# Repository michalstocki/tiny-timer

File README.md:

# Minutnik na ATtiny13A

Firmware w czystym C (`avr-gcc -Os`, bez Arduino core), instrukcja montażu na płytce stykowej, programowanie przez Arduino UNO, kalibracja i testy odbiorcze. Materiały dla użytkownika są po polsku.

| Co | Gdzie |
| --- | --- |
| Instrukcja montażu (kroki, adresy otworów, rysunki, sprawdzenia) | [docs/instrukcja-montazu.md](docs/instrukcja-montazu.md) |
| Programowanie: ArduinoISP, fuse'y, wgrywanie | [docs/programowanie.md](docs/programowanie.md) |
| Kalibracja czasu (OSCCAL) | [docs/kalibracja.md](docs/kalibracja.md) |
| Testy odbiorcze (tabela do wypełnienia) | [docs/testy-odbiorcze.md](docs/testy-odbiorcze.md) |
| Diagnostyka | [docs/diagnostyka.md](docs/diagnostyka.md) |
| Plan B: ATtiny25/45/85 z ramką i dzwonkiem | [docs/plan-b.md](docs/plan-b.md) |
| Netlista i mapa pinów | [docs/schemat.md](docs/schemat.md) |
| Gotowe pliki `.hex` i raport `avr-size` | `dist/` |
| Źródła firmware i `Makefile` | `firmware/` |
| Generator rysunków/instrukcji i weryfikacja sieci | `tools/breadboard/` |
| Symulacja logiki firmware na komputerze | `tools/sim/` |

## Szybki start

```bash
cd firmware
make                                    # buduje i drukuje rozmiary (avr-gcc z PATH lub z Arduino IDE)
make sig   PORT=/dev/cu.usbmodemXXXX    # Etap 1: sygnatura 0x1e9007 (ATtiny w gnieździe programatora)
make fuses PORT=/dev/cu.usbmodemXXXX    # Etap 2
make flash PROG=test_tone PORT=...      # Etapy 3-5: test_tone, test_display, test_buttons
make flash PROG=timer PORT=...          # Etap 6
```

Weryfikacja bez sprzętu:

```bash
tools/sim/run.sh                                 # logika minutnika (ATtiny13A)
SIM_FLAGS="-DFEATURE_BAR=1 -DFEATURE_BELL=1" tools/sim/run.sh   # plan B
SIM_TARGET=calib tools/sim/run.sh                # program kalibracyjny
cd tools/breadboard && python3 design.py && python3 test_design.py
```

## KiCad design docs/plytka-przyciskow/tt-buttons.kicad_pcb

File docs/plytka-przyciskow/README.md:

# Płytka przycisków (obudowa klin 4)

Trzy przyciski Omron B3F-4055 (S3 „−”, S1 „run”, S2 „+”) i cztery przewody do pól KEY płytki głównej. Są dwie wersje o tym samym położeniu przycisków, otworów M2 i pól przewodów:

| Wersja | Dla kogo |
| --- | --- |
| **[Płytka drukowana TT-BTN](#płytka-drukowana-tt-btn-zamówienie-na-pcbway)** (54 × 16 mm, 2 warstwy) | zalecana: bez pracy warsztatowej, zamówienie razem z płytką główną |
| [Płytka uniwersalna](#płytka-przycisków-na-płytce-uniwersalnej) (50 × 16 mm, raster 2,54) | gdy masz płytkę uniwersalną pod ręką i nie chcesz czekać na fabrykę |

## Płytka drukowana TT-BTN (zamówienie na PCBWay)

| Plik | Co to |
| --- | --- |
| [`tt-buttons.kicad_pcb`](tt-buttons.kicad_pcb) | projekt dla KiCada (format v7, sprawdzony w KiCadzie 10.0.7): obrys, stopki, sieci, ścieżki, opisy |
| [`produkcja/tt-buttons-gerber.zip`](produkcja/tt-buttons-gerber.zip) | **plik do wysłania do fabryki**: 7 warstw Gerber, wiercenia PTH i NPTH (Excellon, mm), plik zadania `.gbrjob` |
| `produkcja/` (reszta) | rozpakowane Gerbery, raporty DRC KiCada, mapy wierceń (poza zipem), podglądy `kicad-F.svg` i `kicad-B.svg` |
| [`plytka-przyciskow-pcb-top.png`](plytka-przyciskow-pcb-top.png), [`plytka-przyciskow-pcb-bottom.png`](plytka-przyciskow-pcb-bottom.png) | render KiCada obu stron |

### Zamówienie

Płytka główna ([`docs/plytka-glowna/`](../plytka-glowna/README.md)) i płytka przycisków to **dwa osobne projekty i dwa osobne zamówienia**, oba jako „Single pieces”. Wrzuć oba do jednego koszyka, wtedy wysyłka jest jedna.

| Parametr w formularzu PCBWay | Płytka przycisków | Płytka główna |
| --- | --- | --- |
| Board type | Single pieces | Single pieces |
| Different design in panel | 1 | 1 |
| Size | **54 × 16 mm** | 40 × 24 mm |
| Quantity | 5 | 5 |
| Layers / Material / Thickness | 2 / FR-4 / 1,6 mm | 2 / FR-4 / 1,6 mm |
| Pozostałe | domyślne (HASL, zielona maska, biały opis, miedź 1 oz) | jak w [README płytki głównej](../plytka-glowna/README.md#parametry-do-zamówienia-typowa-fabryka-2-warstwowa-np-jlcpcb-lub-pcbway) |

**Dlaczego nie jeden plik z obiema płytkami (panel).** Sprawdziłem w kalkulatorze PCBWay (15.11.2026, 2 warstwy, FR-4 1,6 mm, opcje domyślne, ceny bez wysyłki). Najniższa stawka obejmuje tylko 5 sztuk **jednego** projektu do 100 × 100 mm. Każde połączenie płytek w jednym pliku podnosi cenę:

| Wariant | Sztuk | Cena |
| --- | --- | --- |
| 1 projekt, Single pieces (40 × 24, 54 × 16 albo do 100 × 100 mm) | 5 | **5,00 USD** |
| to samo | 10 / 20 | 18,69 / 22,33 USD |
| 2 projekty w jednym pliku, Single pieces | 5 | 27,00 USD |
| panel klienta z mostkami, 1 zestaw (główna + przyciski) | 5 paneli | 36,10 USD |
| panel klienta, 2 zestawy, 100 × 50 mm | 5 paneli | 39,99 USD |
| panel klienta, 3 zestawy, 100 × 100 mm | 5 paneli | 47,04 USD |

Dwie osobne płytki to więc 10 USD za 5 kompletów. PCBWay nie nacina też płytek tak małych jak nasze: według jej zasad V-cut wymaga co najmniej 60 × 45 mm. Każdy panel trzeba by łączyć mostkami z otworami, a to ich formularz liczy jako panel klienta („Panel by Customer”, zob. [Confirm the panel way of the boards](https://www.pcbway.com/helpcenter/panel_issues/Confirm_the_panel_way_of_the_boards.html), [PCB Panel Creation](https://www.pcbway.com/pcb_prototype/PCB_Panel_Creation.html), [V-Scoring](https://www.pcbway.com/pcb_prototype/PCB_V_Scoring.html)). Ceny są orientacyjne: kalkulator zaznacza, że cenę ostateczną ustala PCBWay po weryfikacji, i ceny mogą się zmienić.

### Projekt

- **Zarys 54 × 16 mm** z narożnikami R2, o 2 mm szerszy z każdej strony niż płytka uniwersalna. Przy 50 mm otwory skrajnych nóżek (rozstaw 12,5 mm według karty) leżałyby 0,4 mm od krawędzi, a pola wychodziłyby poza płytkę. Przyciski, otwory M2 i pola przewodów są w tych samych miejscach względem obudowy, a w tabeli niżej współrzędne są przesunięte o 2 mm. Szerszy zarys sprawdziłem w modelu obudowy klin 4 (`TT_BB_EXTRA=2` w [`build_wedge4.py`](../../tools/enclosure/build_wedge4.py)): 0 kolizji w 104 parach, zdejmowanie pokrywy bez kolizji.
- **Stopka B3F-4055 według karty:** 4 pola Ø2,2 z otworem Ø1,2 w rozstawie 12,5 × 5,0 mm i dwa otwory **Ø1,8 bez metalizacji na kołki ustalające** (9,0 mm od siebie). Kołków nie trzeba ścinać.
- **Pola przewodów** Ø2,0 z otworem 1,2 mm, jak pola KEY na płytce głównej. Są w tych samych miejscach co oczka G4, G6, N4 i N2 na płytce uniwersalnej. KEY1 (GND) ma pole kwadratowe, tak jak na płytce głównej. Opisy K1…K4 są na obu stronach.
- **Ścieżki** 0,30 mm, ręcznie, pod kątem 45°. Strona lutowania (B.Cu): rzędy nóżek każdego przycisku, GND od S1 do S2 i odejścia do K1, K2 i K4. Strona elementów (F.Cu): jedna ścieżka PB4 od S3 przez K3, osią przycisków pod S1, do S2. Schemat jest ten sam co niżej, nie ma przewodów rozdzielczych.
- **Otwory M2** Ø2,2 bez metalizacji. Miedź trzyma się z daleka od łba wkręta (od strony lutowania) i od słupka pokrywy (od strony elementów): ścieżki co najmniej 2,3 mm od osi, pola 3,4 mm.
- Opisy: oznaczenia S1…S3 i symbole −, RUN, + na stronie elementów. Na stronie lutowania napis TT-BTN v1.0 i strzałka „glosnik ->” wskazująca stronę głośnika. Napisy „TOP” i „BOT” w miedzi, jak na płytce głównej (kontrola, czy warstwy nie są zamienione).

| Element | Położenie [mm] od lewego dolnego narożnika (widok od strony elementów) |
| --- | --- |
| S3 „−”, S1 „run”, S2 „+” (środki) | 9,22 / 27,00 / 44,78; y = 8,00 |
| otwory M2 Ø2,2 | (18,11; 2,92) i (35,89; 13,08) |
| K1 GND (kwadratowe), K2 PB3 | (35,89; 8,00), (35,89; 2,92) |
| K3 PB4, K4 do R6 | (18,11; 8,00), (18,11; 13,08) |

### Montaż

1. Sprawdź przyciski multimetrem (krok 0 niżej). Wynik decyduje o schemacie.
2. Włóż trzy przyciski od strony elementów (kołki wchodzą w otwory Ø1,8), dociśnij do laminatu i zalutuj od strony lutowania (12 lutów). Nie myj płytki z przyciskami.
3. Przewody KEY1…KEY4 przełóż od strony lutowania przez pola K1…K4 i zalutuj od strony elementów, z końcówką do 1 mm (nad płytką jest 6,8 mm do sufitu pokrywy). Kolory i pola płytki głównej jak w tabeli „Połączenia na płytce” niżej.
4. Kontrola multimetrem jak w kroku 10 niżej. Montaż w pokrywie: dwa wkręty M2 × 6 od strony lutowania, lewa krawędź (strzałka „glosnik ->”) od strony głośnika.

### Co sprawdziłem

- **Kontrola własna** ([`tools/pcb/fab_buttons.py`](../../tools/pcb/fab_buttons.py)): każda z 4 sieci w jednym kawałku, odstęp miedzi co najmniej 0,25 mm (najmniejszy jest **0,35 mm**), miedź co najmniej 0,5 mm od krawędzi, otwory kołków i M2 ze strefami wolnymi od miedzi. Test ujemny: usunięta ścieżka, ścieżka przy polu innej sieci i ścieżka przy M2 są wykrywane. Pierwsza wersja trasy przechodziła 0,13 mm od narożnika kwadratowego pola KEY1. Wykrył to DRC KiCada, bo moja kontrola liczyła pola jako okrągłe. Kontrola liczy teraz kwadraty jako kwadraty i na starej trasie podaje te same odległości co KiCad.
- **KiCad 10.0.7** ([`export_fab.sh`](../../tools/pcb/export_fab.sh)): DRC bez błędów, 0 niepołączonych pól. Zostało 9 ostrzeżeń o braku biblioteki `TT` (stopki są wbudowane w plik). Gerbery i wiercenia: PTH Ø1,2 (12 nóżek i 4 pola przewodów), NPTH Ø1,8 (6 kołków) i Ø2,2 (2 × M2).
- **Nie sprawdziłem** podglądu Gerberów w PCBWay (wymaga wgrania pliku na ich stronę) ani dopasowania na fizycznym B3F-4055. Po wgraniu zipa sprawdź, czy PCBWay rozpoznał 2 warstwy i wymiar 54 × 16 mm.

### Regeneracja

```bash
python3 tools/pcb/fab_buttons.py                                                                 # kontrola + tt-buttons.kicad_pcb
bash tools/pcb/export_fab.sh docs/plytka-przyciskow/tt-buttons.kicad_pcb docs/plytka-przyciskow/produkcja   # DRC KiCada, Gerbery, zip
```

## Płytka przycisków na płytce uniwersalnej

Trzy przyciski Omron B3F-4055 (S3 „−”, S1 „run”, S2 „+”) na kawałku jednostronnej płytki uniwersalnej **50 × 16 mm**, z czterema przewodami do pól KEY płytki głównej. Zarys, otwory M2 i rozstaw przycisków są zgodne z [obudową klin 4](../obudowa-klin-4/README.md#5-płytka-przycisków-na-płytce-uniwersalnej) (dane: [`pcb-layout.json`](../pcb-klin3/pcb-layout.json), klucz `button_board`).

**Do druku: [`plytka-przyciskow-szablon.pdf`](plytka-przyciskow-szablon.pdf)** (A4, 4 strony):

| Strona | Treść |
| --- | --- |
| 1 | **Szablon 1:1** od strony elementów: zarys z narożnikami R2, siatka oczek, otwory M2 Ø2,2, obrysy przycisków, tabela współrzędnych, linijka kontrolna 100 mm |
| 2 | **Połączenia** od strony lutowania w skali 3:1: adresy oczek, 6 przewodów rozdzielczych, 4 pola KEY, lista przewodów z kolorami i długościami |
| 3 | **Schemat elektryczny**, wnętrze przycisku wg karty, kontrola multimetrem |
| 4 | Lista części i narzędzi, kolejność montażu, najczęstsze pułapki |

Te same strony jako SVG: `plytka-przyciskow-{szablon,polaczenia,schemat,montaz}.svg`. Generator i kontrola projektu: [`tools/pcb/button_board.py`](../../tools/pcb/button_board.py).

```bash
python3 tools/pcb/button_board.py           # kontrola + PDF/SVG w tym katalogu (wymaga rsvg-convert)
python3 tools/pcb/button_board.py --check   # tylko kontrola
```

## Założenie: przycisk zgodny z kartą

Projekt przyjmuje budowę z karty Omron B3F (A070-E1-08, s. 6, model B3F-4055 „projected plunger, bez nóżki masy”):

| Co | Wartość z karty |
| --- | --- |
| Połączenia wewnętrzne (widok z góry) | **4–3 i 2–1 połączone na stałe**, wciśnięcie zwiera górny rząd z dolnym |
| Nóżki | 4 szt., **12,5 × 5,0 mm** (±0,1), otwory w płytce Ø1,2 (±0,05); blaszki ok. 1,0 × 0,3 mm (odczyt z rysunku), 3,5 mm pod korpusem |
| Kołki ustalające | 2 szt. Ø1,6 (otwory Ø1,8), **9,0 mm** od siebie, na osi między kolumnami nóżek |
| Korpus, wysokość, trzpień | 12 × 12 mm, 7,3 mm nad płytką (korpus 4,3), trzpień 3,8 × 3,8 mm |
| Siła, skok | 2,55 ±0,69 N, skok 0,3 mm; obciążenie 1…50 mA, 3…24 V; mycie niemożliwe |

To rozstrzyga sprzeczność z wcześniejszej specyfikacji (`docs/pcb/specyfikacja-obudowy-dla-agenta.md`, punkt 7: „wg pomiaru właściciela 5 mm”): **nóżki połączone na stałe dzieli 12,5 mm**, nie 5 mm. Numery nóżek nie są nadrukowane na obudowie przycisku, więc w projekcie rozróżnia się je po położeniu: para nóżek rozstawionych o 12,5 mm to jeden „rząd”.

Skoro założenie decyduje o schemacie, pierwszym krokiem montażu jest **sprawdzenie ciągłości na samych przyciskach** (strona 3 i 4 PDF). Jeśli wynik wyjdzie odwrotnie, nie lutuj dalej.

## Płytka uniwersalna

- Jednostronna FR4 **1,6 mm**, raster **2,54 mm**, **osobne pola lutownicze** (nie płytka paskowa: paski zwarłyby nóżki). Kawałek co najmniej 55 × 20 mm, wygodniej 70 × 30 mm.
- Przed zakupem lub użyciem sprawdź raster: skrajne oczka rzędu na płytce mają trafić w kropki A i T szablonu (19 odstępów = 48,26 mm). Płytki o rastrze 2,5 mm się nie nadają.
- Oczka Ø1,0 mogą być za ciasne dla blaszki 1,0 × 0,3 mm (przekątna ok. 1,05 mm): jeśli nóżka wchodzi z oporem, rozwierć oczko pod nóżkę do Ø1,2, zgodnie z kartą.

## Geometria i raster

Siatka oczek leży tak, że wszystkie nóżki przycisków trafiają w oczka. Adres oczka to **kolumna A…T + rząd 1…7** w widoku od strony elementów (x w prawo, y w górę), jak na szablonie.

| Element | Położenie [mm] od lewego dolnego narożnika | Oczko |
| --- | --- | --- |
| przycisk S3 „−” (środek) | 7,22; 8,00 | nóżki A3, F3 (dół), A5, F5 (góra) |
| przycisk S1 „run” | 25,00; 8,00 | H3, M3, H5, M5 |
| przycisk S2 „+” | 42,78; 8,00 | O3, T3, O5, T5 |
| otwór M2-1 Ø2,2 | 16,11; 2,92 | G2 |
| otwór M2-2 Ø2,2 | 33,89; 13,08 | N6 |

- Pierwsze oczko (A1) jest w (0,87; 0,38), ostatnie (T7) w (49,13; 15,62). Raster ma 20 kolumn × 7 rzędów, a środki przycisków leżą w połowie oczka (x) i na rzędzie 4 (y).
- Rozstaw oczek 12,70 mm kontra 12,50 mm w karcie: oczka są o 0,10 mm na każdą stronę dalej niż otwory zalecane, w granicach tolerancji karty (nóżki są sprężyste). Odchyłka w osi y to 0,04 mm. Generator sprawdza to przy każdym uruchomieniu.
- **Skrajne rzędy oczek (1 i 7) leżą 0,38 mm od krawędzi, więc linia cięcia przetnie ich oczka.** Nie są używane. Nie da się tego uniknąć bez zmiany obudowy: rzędy nóżek (y = 5,46 i 10,54) wyznaczają fazę rastra. Skrajne kolumny (A i T) są 0,87 mm od krawędzi i zostają prawie całe.
- Dwa otwory M2 leżą na oczkach, po przekątnej, pomiędzy przyciskami (słupki w pokrywie nie wchodzą w korpusy: sprawdzone wymiarowo).

## Schemat

| Przycisk | Górny rząd (nóżki 4–3) | Dolny rząd (nóżki 2–1) | Zwiera |
| --- | --- | --- | --- |
| S1 „run” | KEY1 (GND) | KEY2 (PB3) | KEY1–KEY2 |
| S2 „+” | KEY1 (GND) | KEY3 (PB4) | KEY1–KEY3 |
| S3 „−” | KEY4 (do R6, potem GND) | KEY3 (PB4) | KEY3–KEY4 |

Zgodne z [`docs/schemat.md`](../schemat.md): PB3 ma wewnętrzny pull-up, PB4 ma R5 8,2 kΩ do VCC, a „−” przechodzi przez R6 8,2 kΩ do GND (R6 jest na płytce głównej). Kontrola w generatorze buduje sieć z rysunku (nóżki, przewody, wewnętrzne połączenia przycisku) i sprawdza wszystkie 8 kombinacji wciśniętych przycisków: puszczone dają cztery osobne pola, a każdy przycisk zwiera dokładnie swoją parę. Wykrywa to błędy typu przewód na złym rzędzie albo pole KEY w złym oczku (sprawdziłem na celowo zepsutych wariantach).

## Połączenia na płytce

Wszystko po stronie lutowania, widok na stronie 2 PDF (obrócony jak kartka wokół osi pionowej, więc kolumny idą T → A).

| Nr | Od | Do | Sieć | Kolor | Trasa |
| --- | --- | --- | --- | --- | --- |
| W1 | M5 (S1, nóżka 3) | N4 | GND | czarny | 3,6 mm |
| W2 | O5 (S2, nóżka 4) | N4 | GND | czarny | 3,6 mm |
| W3 | M3 (S1, nóżka 1) | N2 | PB3 | pomarańczowy | 3,6 mm |
| W4 | F3 (S3, nóżka 1) | G4 | PB4 | niebieski | 3,6 mm |
| W5 | O3 (S2, nóżka 2) | G4 | PB4 | niebieski | 22,9 mm, rowkiem między rzędami 3 i 4 |
| W6 | F5 (S3, nóżka 3) | G6 | KEY4 | zielony | 3,6 mm |
| KEY1 | N4 | płytka główna | GND | czarny | |
| KEY2 | N2 | płytka główna | PB3 | pomarańczowy | |
| KEY3 | G4 | płytka główna | PB4 | niebieski | |
| KEY4 | G6 | płytka główna | do R6 | zielony | |

- Pola przewodu leżą w dwóch kolumnach między przyciskami (G i N), poza korpusami, więc przewód można przewlec z oczka na stronę elementów. Dwa przewody idą do jednej kolumny, dwa do drugiej: kabel z płytki głównej wystarczy rozdzielić na pary.
- Pozostałe nóżki (np. H5, T3) są po prostu przylutowane: wewnętrzne połączenie przycisku łączy je z sąsiadką.
- Oczka N4 i G4 mają po trzy przewody (kabel + dwa rozdzielcze): użyj cienkich przewodów rozdzielczych Ø0,25 (wire-wrap AWG30).
- Przewód W5 biegnie 3,8 mm od osi wkręta M2 w G2 (łeb Ø4 ma promień 2 mm). Generator pilnuje, żeby trasy przewodów były co najmniej 2,3 mm, a używane oczka co najmniej 3,4 mm od osi M2.
- Kolory kabla do płytki głównej to propozycja. Ważne, żeby zapisać, który przewód jest którym polem KEY.

## Instrukcja montażu

**Części:** 3 × Omron B3F-4055 (nie B3F-4155: ma piątą nóżkę), płytka uniwersalna jak wyżej, 6 przewodów rozdzielczych w izolacji Ø0,25 (razem ok. 10 cm), 4 linki 0,14 mm² w kolorach z tabeli, 2 wkręty samogwintujące M2 × 6, cyna z topnikiem bezmyjnym. **Narzędzia:** wiertła Ø1,0 i Ø2,2 (opcjonalnie Ø1,2), imadło, piła do laminatu lub miniszlifierka, pilnik, nożyk, szczypce tnące, multimetr, lutownica z grotem 1…2 mm.

0. **Sprawdź przyciski** (przed czymkolwiek). Multimetrem w zakresie ciągłości: nóżki rozstawione o 12,5 mm w jednym rzędzie (4–3 oraz 2–1) mają ciągłość zawsze, a nóżki w tej samej kolumnie (4–2, 3–1; 5,0 mm) tylko po wciśnięciu. Jeśli jest odwrotnie, przycisk nie jest zgodny z kartą: zatrzymaj się i zmierz sześć par nóżek.
1. **Wydrukuj stronę 1 w skali 100 %** (w oknie drukowania „Rzeczywisty rozmiar”, bez „Dopasuj do strony”). Odcinek 100 mm i kwadrat 20 × 20 mm sprawdź linijką. Dokładność wydruku nie ma tu znaczenia dla oczek (te są na płytce), ale ma dla linii cięcia i otworów M2.
2. **Przyłóż szablon do płytki** tak, by kropki szablonu (także szare, poza zarysem) pokryły się z oczkami płytki; zamocuj kawałkiem taśmy lub klejem w sztyfcie. Środki M2 nakłuj igłą przez papier (krzyżyki wskazują środek), zdejmij szablon. Linię cięcia możesz odrysować rysikiem.
3. **Wywierć M2:** płytka w imadle na drewnianej podkładce, najpierw Ø1,0, potem Ø2,2 (otwór ma być 2,2, bo wkręt idzie przez niego do słupka pokrywy). Rób to przed cięciem, kiedy płytka jest jeszcze duża.
4. **Wytnij zarys** 50 × 16 mm (zostaw 0,2 mm na pilnik), opiłuj do linii, zaokrąglij narożniki R2, usuń zadziory pilnikiem lub papierem. Dopuszczalna odchyłka wymiaru ok. ±0,3 mm (kapsle mają w otworach pokrywy 0,3 mm luzu, a płytka trzyma się na słupkach, więc ważniejsze od zarysu jest położenie M2 i przycisków). Pył z laminatu: maska i przewiew.
5. **Kołki ustalające przycisków** odetnij nożykiem lub szczypcami równo z korpusem (od spodu). To zalecany wariant: kołki nie trafiają w oczka (leżą 0,58 mm od rzędu oczek), a cztery luty trzymają przycisk w zupełności. Alternatywa: wywierć Ø1,8 według tabeli na stronie 1 (zniszczy to też brzegi sąsiednich oczek, które i tak nie są używane).
6. **Przymierz nóżki** przycisków w oczkach (bez lutowania). Nóżki są sprężyste i lekko zbiegają się (12,5 mm kontra 12,7 mm oczek), ale powinny wejść bez wciskania na siłę. Jeśli nie: rozwierć oczka pod nóżki Ø1,2.
7. **Włóż trzy przyciski** od strony elementów, korpusem do laminatu, bokami równolegle do krawędzi płytki (dłuższy rozstaw nóżek 12,5 mm wzdłuż płytki). Zalutuj po jednej nóżce, sprawdź, czy korpus leży płasko i prosto (ew. przegrzej i popraw), dopiero potem pozostałe, razem 12 lutów. Lutuj krótko, kilka sekund na nóżkę. **Nie myj** płytki z przyciskami (karta: mycie niemożliwe), resztki topnika bezmyjnego zostaw.
8. **Przewody rozdzielcze W1…W6** wg tabeli: zdejmij 1,5 mm izolacji, przewlecz lub przyłóż końcówkę do pola, zalutuj. Przewód układaj płasko przy laminacie (po stronie lutowania wystają końcówki nóżek do 1,9 mm: przewody nie powinny sięgać wyżej niż one) i z dala od czerwonych okręgów M2 (łeb wkręta).
9. **Cztery przewody do płytki głównej** (KEY1…KEY4) wlutuj w pola N4, N2, G4, G6 (przewód od strony lutowania przez oczko, końcówka po stronie elementów max 1 mm i utnij ją równo z laminatem; nad płytką od tej strony jest 6,8 mm do sufitu pokrywy). Długość: do ustalenia po złożeniu pokrywy (przewody od strony lutowania zbieraj ku płytce głównej, z luzem 10…15 mm).
10. **Kontrola multimetrem** (strona 3): puszczone: wszystkie pary KEY rozwarte; S1 zwiera KEY1–KEY2, S2 zwiera KEY1–KEY3, S3 zwiera KEY3–KEY4, a przy żadnym z nich nie ma innych zwarć.
11. **Montaż w pokrywie:** płytkę dołóż od wnętrza do słupków i przykręć dwoma wkrętami M2 × 6 od strony lutowania (łeb wkręta nie może leżeć na lutach ani przewodach). Na trzpienie przycisków wciśnij kapsle. Przycisk powinien dać wyraźne „kliknięcie” przez kapsel.

## Zgodność z obudową

- Trzpienie 7,3 mm nad płytką, kapsle i gniazda są z [klina 4](../obudowa-klin-4/README.md#4-kapsle-przycisków-b3f-4055); płytka trzyma się na słupkach z otworem Ø1,7 (pod M2 × 6).
- Płytka jest elementami do pokrywy, lutami do wnętrza. Ta strona jest w obudowie widoczna na renderze `12-pokrywa-od-srodka.png`: otwory M2 są na nim w lewym górnym i prawym dolnym rogu, co zgadza się z odbiciem na stronie 2 PDF (M2-2 po lewej u góry, M2-1 po prawej na dole).
- Oś x płytki jest osią obudowy: lewa krawędź (x = 0) jest od strony głośnika. Przycisk „−” (S3) jest przy głośniku, „+” (S2) przy prawym boku. Obrócenie płytki o 180° zamieni przyciski miejscami względem kapsli.

## Czego nie sprawdziłem i ryzyka

1. **Prawdziwe części.** Wszystko wynika z karty i z modelu obudowy, nic nie jest zmierzone na fizycznym B3F-4055 ani na konkretnej płytce uniwersalnej. Krok 0 i przymiarka (krok 6) są po to, żeby to wyłapać zanim cokolwiek zalutujesz.
2. **Karta nie podaje warunków lutowania** (w pliku jest tylko „mycie niemożliwe”): lutuj krótko i bez przegrzewania. Parametry ogólne Omron dla przełączników dotykowych leżą w osobnym dokumencie „Safety Precautions”, którego nie sprawdzałem.
3. **Skrajne rzędy oczek** są przecięte linią cięcia (punkt wyżej): to wynika z geometrii obudowy i nie wpływa na działanie. Jeśli zależy Ci na czystym brzegu, trzeba by zmienić rozstaw przycisków albo wymiar obudowy.
4. **Przewody i luz w pokrywie:** wysokość lutów i przewodów po stronie lutowania nie była sprawdzana modelem 3D (przyjęto do 1,9 mm jak dla nóżek).
5. **Płytka główna** ma osobny projekt i pliki produkcyjne w [`docs/plytka-glowna/`](../plytka-glowna/README.md); wersja drukowana płytki przycisków jest opisana na początku tego pliku.

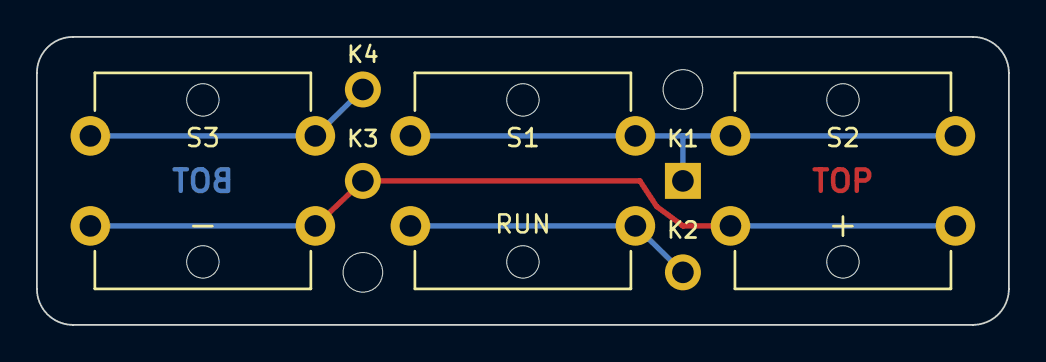
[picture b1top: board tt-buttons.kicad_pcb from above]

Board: 2 copper layers, 54.0 x 16.0 mm, 9 parts (0 on the bottom side), 4 nets.

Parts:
KEY1: GND; Wire_Pad_D2.0
KEY2: PB3; Wire_Pad_D2.0
KEY3: PB4; Wire_Pad_D2.0
KEY4: KEY4; Wire_Pad_D2.0
MH1, MH2: M2; MountingHole_M2
S1, S2, S3: B3F-4055; SW_Omron_B3F-4055

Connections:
GND: KEY1.1, S1.3, S1.4, S2.3, S2.4
KEY4: KEY4.1, S3.3, S3.4
PB3: KEY2.1, S1.1, S1.2
PB4: KEY3.1, S2.1, S2.2, S3.1, S3.2

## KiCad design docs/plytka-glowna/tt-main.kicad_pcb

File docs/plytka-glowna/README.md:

# Płytka główna (klin 4): projekt do zamówienia

Dwuwarstwowa płytka **40 × 24 mm** z elementami THT dla obudowy [klin 4](../obudowa-klin-4/README.md). Rozmieszczenie, zarys, otwory M2,5 i wysokości są z [`pcb-klin3`](../pcb-klin3/README.md) i **nie zostały zmienione**, więc model obudowy pozostaje ważny. Nowe jest trasowanie, stopki produkcyjne, opisy i pliki do fabryki.

**Status: Gerbery wyeksportowane i sprawdzone w KiCadzie 10.0.7** (DRC KiCada bez błędów, także z regułą odstępu 0,25 mm; Gerbery obejrzane w GerbView). Do fabryki wysyłasz [`produkcja/tt-main-gerber.zip`](produkcja/tt-main-gerber.zip). Przed zamówieniem zmierz jeszcze wysokość C3 (ryzyko 2).

## Pliki

| Plik | Co to |
| --- | --- |
| [`tt-main.kicad_pcb`](tt-main.kicad_pcb) | projekt dla KiCada (format v7, sprawdzony w KiCadzie 10.0.7): obrys, otwory, stopki, sieci, ścieżki, opisy |
| [`trasowanie.json`](trasowanie.json) | zapisane trasowanie (źródło dla pliku KiCada) |
| [`plytka-strona-elementow.svg`](plytka-strona-elementow.svg), [`plytka-strona-lutowania.svg`](plytka-strona-lutowania.svg) | podglądy obu stron z miedzią i opisami |
| [`plan-montazu.svg`](plan-montazu.svg), [`plan-pomiarow.svg`](plan-pomiarow.svg) | rysunki do instrukcji |
| [`instrukcja-montazu.md`](instrukcja-montazu.md) | montaż krok po kroku z kontrolami |
| [`bom.csv`](bom.csv) | lista części |
| [`produkcja/tt-main-gerber.zip`](produkcja/tt-main-gerber.zip) | **plik do wysłania do fabryki**: 7 warstw Gerber, wiercenia PTH i NPTH (Excellon, mm), plik zadania `.gbrjob` |
| `produkcja/` (reszta) | wynik `export_fab.sh`: rozpakowane Gerbery (`gerber/`), raporty DRC KiCada (`drc-kicad.txt`, `drc-kicad-bledy.txt`), mapy wierceń (`mapa-wiercen/`, poza zipem), podglądy `kicad-F.svg` i `kicad-B.svg` |

## Parametry do zamówienia (typowa fabryka 2-warstwowa, np. JLCPCB lub PCBWay)

| Parametr | Wartość |
| --- | --- |
| Warstwy / materiał | 2, FR-4, 1,6 mm, miedź 1 oz (35 µm) |
| Wymiary | 40 × 24 mm, narożniki R3, tolerancja zarysu ±0,2 mm (obudowa przyjmuje ±0,3) |
| Wykończenie pól | HASL bezołowiowy (do lutowania ręcznego wystarczy; ENIG droższy, bez zalet tutaj) |
| Maska, opis | domyślna zielona maska i biały opis |
| Najmniejsza ścieżka / odstęp | 0,30 / 0,28 mm w projekcie (fabryki dają 0,127 mm, więc duży zapas) |
| Najmniejsze wiercenie | 0,4 mm (przelotka, 1 szt.), pola 0,8…1,2 mm, otwór M2,5: 2,7 mm niemetalizowany |
| Liczba sztuk | najmniejsza oferowana (zwykle 5); wystarczy do próby i zapasu |
| Pozostałe opcje | domyślne; fabryka może dodać numer zamówienia na płytce (w miejscu bez miedzi), na ogół można go wyłączyć za dopłatą |

Nazwy opcji w formularzach fabryk różnią się, ale wszystkie powyższe wartości są standardowe. **Zamów kilka sztuk**: płytka jest mała i tania, a pierwsza wersja zawsze może wymagać poprawki.

**Płytka przycisków** ma osobny projekt i osobne Gerbery: [`docs/plytka-przyciskow/`](../plytka-przyciskow/README.md#płytka-drukowana-tt-btn-zamówienie-na-pcbway). Zamawiaj obie jako dwie pozycje „Single pieces” w jednym koszyku. Panel z obiema płytkami kosztuje w PCBWay kilka razy więcej (porównanie cen w tamtym README).

## Co sprawdziłem

- **DRC własny** ([`tools/pcb/fab_drc.py`](../../tools/pcb/fab_drc.py)), na dokładnej geometrii: 0 błędów. Najmniejszy odstęp miedzi **0,28 mm** (wymagane 0,25), miedź ≥ 0,5 mm od krawędzi płytki, miedź ≥ 3,0 mm od osi otworów M2,5, pierścienie pól ≥ 0,4 mm, przelotka 0,8/0,4 (pierścień 0,2 mm), odstęp otworów ≥ 1,18 mm. Test ujemny: usunięta ścieżka, ścieżka w polu innej sieci i miedź przy krawędzi są wykrywane.
- **Łączność (LVS):** z geometrii miedzi wyliczona łączność jest zgodna z netlistą: każda z 12 sieci w jednym kawałku, 0 zwarć.
- **Netlista** zgodna z referencją z [`tools/breadboard/design.py`](../../tools/breadboard/design.py) (ta sama, z której powstała instrukcja na płytce stykowej), po pominięciu przycisków, modułu OLED i opcjonalnych R7/R8.
- **Zgodność z obudową:** żaden element nie został przesunięty, obrysy i wysokości są z `board.py`, więc wynik kolizji z [README klina 4](../obudowa-klin-4/README.md) pozostaje ważny. Zmienił się tylko rozstaw nóżek C3 (patrz niżej), w obrysie elementu.

- **KiCad 10.0.7** (`export_fab.sh`): plik wczytuje się bez błędów; DRC KiCada: 0 błędów, 0 niepołączonych pól. Zostały same dopuszczalne ostrzeżenia: 18 × brak biblioteki `TT` (stopki są wbudowane w plik), 32 × obrys elementu na polu (maska go przytnie), 4 × stykające się obrysy C2 i C3. Dodatkowo DRC z ostrzejszymi regułami (odstęp 0,25 mm, miedź–krawędź 0,5 mm, otwór–otwór 0,5 mm): 0 błędów; test ujemny z odstępem 0,29 mm wskazuje dwa miejsca z 0,28 mm przy U1.5, czyli KiCad liczy to samo co własny DRC.
- **Napisy w miedzi** (na prośbę fabryki, do kontroli, że warstwy nie są zamienione ani odbite): „TOP” na F.Cu w prawym górnym rogu strony elementów i „BOT” na B.Cu nad napisem TT-MAIN, lustrzany, więc czyta się od strony lutowania. Wysokość 1,2 mm, kreska 0,25 mm, bez sieci. Miejsce wybiera [`fab_cutext.py`](../../tools/pcb/fab_cutext.py): największy odstęp od miedzi, poza opisami i strefami otworów M2,5. DRC KiCada nie zgłasza ich nawet przy odstępie 0,4 mm; na renderze obu stron czytają się prosto.
- **Gerbery** obejrzane w GerbView (wszystkie warstwy razem) i sprawdzone w plikach: obrys 40 × 24 mm z R3, 43 pola, 1 przelotka i napis (TOP/BOT) na obu warstwach miedzi, 45 otworów w masce na każdej stronie (43 pola + 2 otwory M2,5; przelotka pod maską), opis B odbity poprawnie, wiercenia PTH Ø0,4 (przelotka), Ø0,8, Ø0,9, Ø1,2 i osobny plik NPTH z 2 × Ø2,7.
- **Poprawka po pierwszym eksporcie:** napis „TT-MAIN v1.0” wychodził 0,4 mm poza narożnik płytki, bo generator opisów zakładał zbyt wąską czcionkę (0,62 zamiast zmierzonych 0,83 wysokości na znak) i nie sprawdzał łuków narożników. Po poprawce w [`fab_silk.py`](../../tools/pcb/fab_silk.py) opisy przesunęły się o ułamki milimetra (napis DISP na stronie lutowania jest teraz pod polami), żaden nie zniknął; elementy, pola i ścieżki bez zmian.

## Zmiany względem projektu `pcb-klin3`

| Zmiana | Po co |
| --- | --- |
| C3 (elektrolit Ø5 mm): rozstaw nóżek 2,0 mm zamiast 2,54 mm | taki masz kondensator; nóżki leżą teraz na polach bez odginania |
| Pola przewodów (DISP, KEY, SPK, BAT) Ø2,0 mm zamiast Ø2,3 mm, otwór 1,2 mm | Ø2,3 na rozstawie 2,54 mm zostawiało 0,24 mm przerwy między polami SPK i BAT |
| Kwadratowe pola: pin 1 U1, plus C3, anoda D1, **BAT+**, KEY1 (GND), DISP1 (SDA) | rozpoznanie polaryzacji i początku grupy bez opisu |
| Nowe trasowanie (czysty router 45°, 1 przelotka, 276 mm ścieżek) | poprzednie było tylko próbą wykonalności na siatce 0,25 mm |
| Opisy: oznaczenia i obrysy elementów (strona elementów), nazwy pól i numery pinów (strona lutowania) | ułatwienie montażu i pomiarów |
| Napisy „TOP” / „BOT” w miedzi | wymaganie fabryki: kontrola strony i odbicia warstw po wytrawieniu |

## Ryzyka i rzeczy do sprawdzenia przed zamówieniem

1. **Podgląd fabryki.** Pliki sprawdziłem w KiCadzie, ale nie w podglądzie Gerberów u fabryki (wymaga wgrania na jej stronę). Po wgraniu zipa sprawdź, czy fabryka rozpoznała 2 warstwy i wymiar 40 × 24 mm i czy obrazek zgadza się z `produkcja/kicad-F.svg`.
2. **Wysokość C3.** Model obudowy zakłada **8,0 mm** (to założenie z [specyfikacji płytki](../pcb-klin3/specyfikacja-plytki.md), nie pomiar). Typowy elektrolit 100 µF/16 V Ø5 mm ma 11 mm, więc ten, który masz, może nie mieścić się pod sufitem obudowy. Zmierz go suwmiarką przed zamówieniem płytki: jeśli ma 11 mm, potrzebna jest niższa wersja (Ø5 × 7 mm, o ile dostępna) albo sprawdzenie, ile miejsca naprawdę jest nad C3 w modelu obudowy.
3. **Opisy na gęstej płytce.** Nie wszystkie opisy pól się zmieściły (np. pełna lista pinów DISP i KEY, plus BAT). Zamiast urwanych napisów jest nazwa grupy albo nic, a kolejność pinów i kwadratowe pole = pin 1 opisuje [instrukcja](instrukcja-montazu.md) i `plan-pomiarow.svg`.
4. **Grubość opisu 0,15 mm i wysokość 1,0 mm** są na dolnej granicy czytelności u tanich fabryk. Jeśli opis wyjdzie nieczytelny, nie ma to wpływu na działanie.
5. **Brak zabezpieczenia przed odwrotną polaryzacją baterii.** Tak jest w schemacie projektu: kwadratowe pole BAT+ i opis w instrukcji mają to ograniczyć.
6. Pozostałe założenia (wymiary modułu OLED, wysokości elementów, położenie koszyka) są takie jak w [README klina 4](../obudowa-klin-4/README.md).

## Regeneracja

```bash
python3 tools/pcb/fab_build.py              # DRC/LVS, plik KiCada, podglądy, BOM (używa zapisanego trasowania)
python3 tools/pcb/fab_build.py --reroute    # trasuje od nowa (1-3 min) i nadpisuje trasowanie.json
bash tools/pcb/export_fab.sh                # (komputer z KiCadem 8-10) DRC KiCada + Gerbery + wiercenia + zip
```

Moduły: [`fab.py`](../../tools/pcb/fab.py) (stopki, pola, opisy), [`fab_router.py`](../../tools/pcb/fab_router.py), [`fab_drc.py`](../../tools/pcb/fab_drc.py), [`fab_silk.py`](../../tools/pcb/fab_silk.py), [`fab_cutext.py`](../../tools/pcb/fab_cutext.py) (napisy w miedzi), [`fab_kicad.py`](../../tools/pcb/fab_kicad.py), [`fab_render.py`](../../tools/pcb/fab_render.py), [`fab_plan.py`](../../tools/pcb/fab_plan.py).

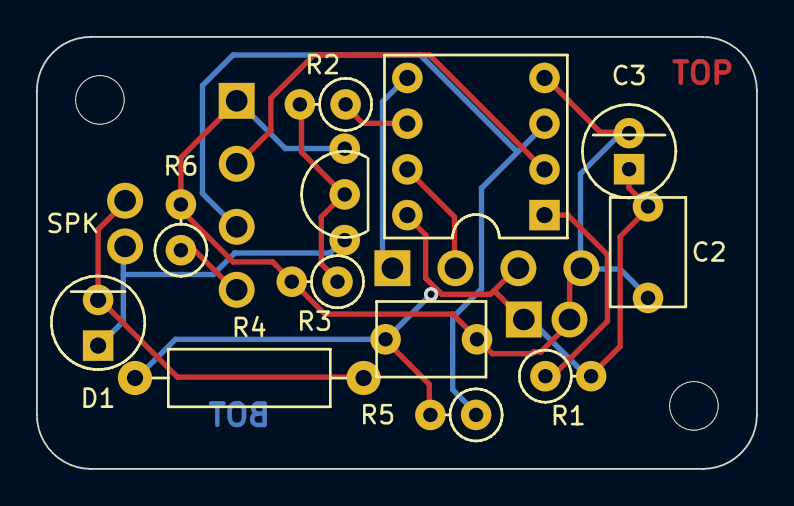
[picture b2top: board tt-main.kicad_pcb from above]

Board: 2 copper layers, 40.0 x 24.0 mm, 18 parts (0 on the bottom side), 12 nets.

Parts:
BAT: battery leads; wire2
C1, C2: 100 nF; cap5
C3: 100 uF; elco5
D1: LED; led
DISP: display module leads; wire4
KEY: button board leads; wire4
MH1, MH2: M2.5; MountingHole_M2.5
Q1: BC547B; to92
R1: 15 k; res_v
R2: 470; res_v
R3: 47 k; res_v
R4: 33, 1/2 W; res_h
R5, R6: 8.2 k; res_v
SPK: speaker leads; wire2
U1: ATtiny13A in DIP-8 socket; dip8

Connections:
BASE: Q1.B, R2.2, R3.1
COLL: D1.A, Q1.C, SPK.2
GND: BAT.2, C1.1, C2.1, C3.-, DISP.4, KEY.1, Q1.E, R3.2, R6.2, U1.4
PB1: R2.1, U1.6
PB3: KEY.2, U1.2
PB4: KEY.3, R5.1, U1.3
RESET: R1.1, U1.1
S3LOW: KEY.4, R6.1
SCL: DISP.2, U1.7
SDA: DISP.1, U1.5
SPKR: D1.K, R4.1, SPK.1
VCC: BAT.1, C1.2, C2.2, C3.+, DISP.3, R1.2, R4.2, R5.2, U1.8
